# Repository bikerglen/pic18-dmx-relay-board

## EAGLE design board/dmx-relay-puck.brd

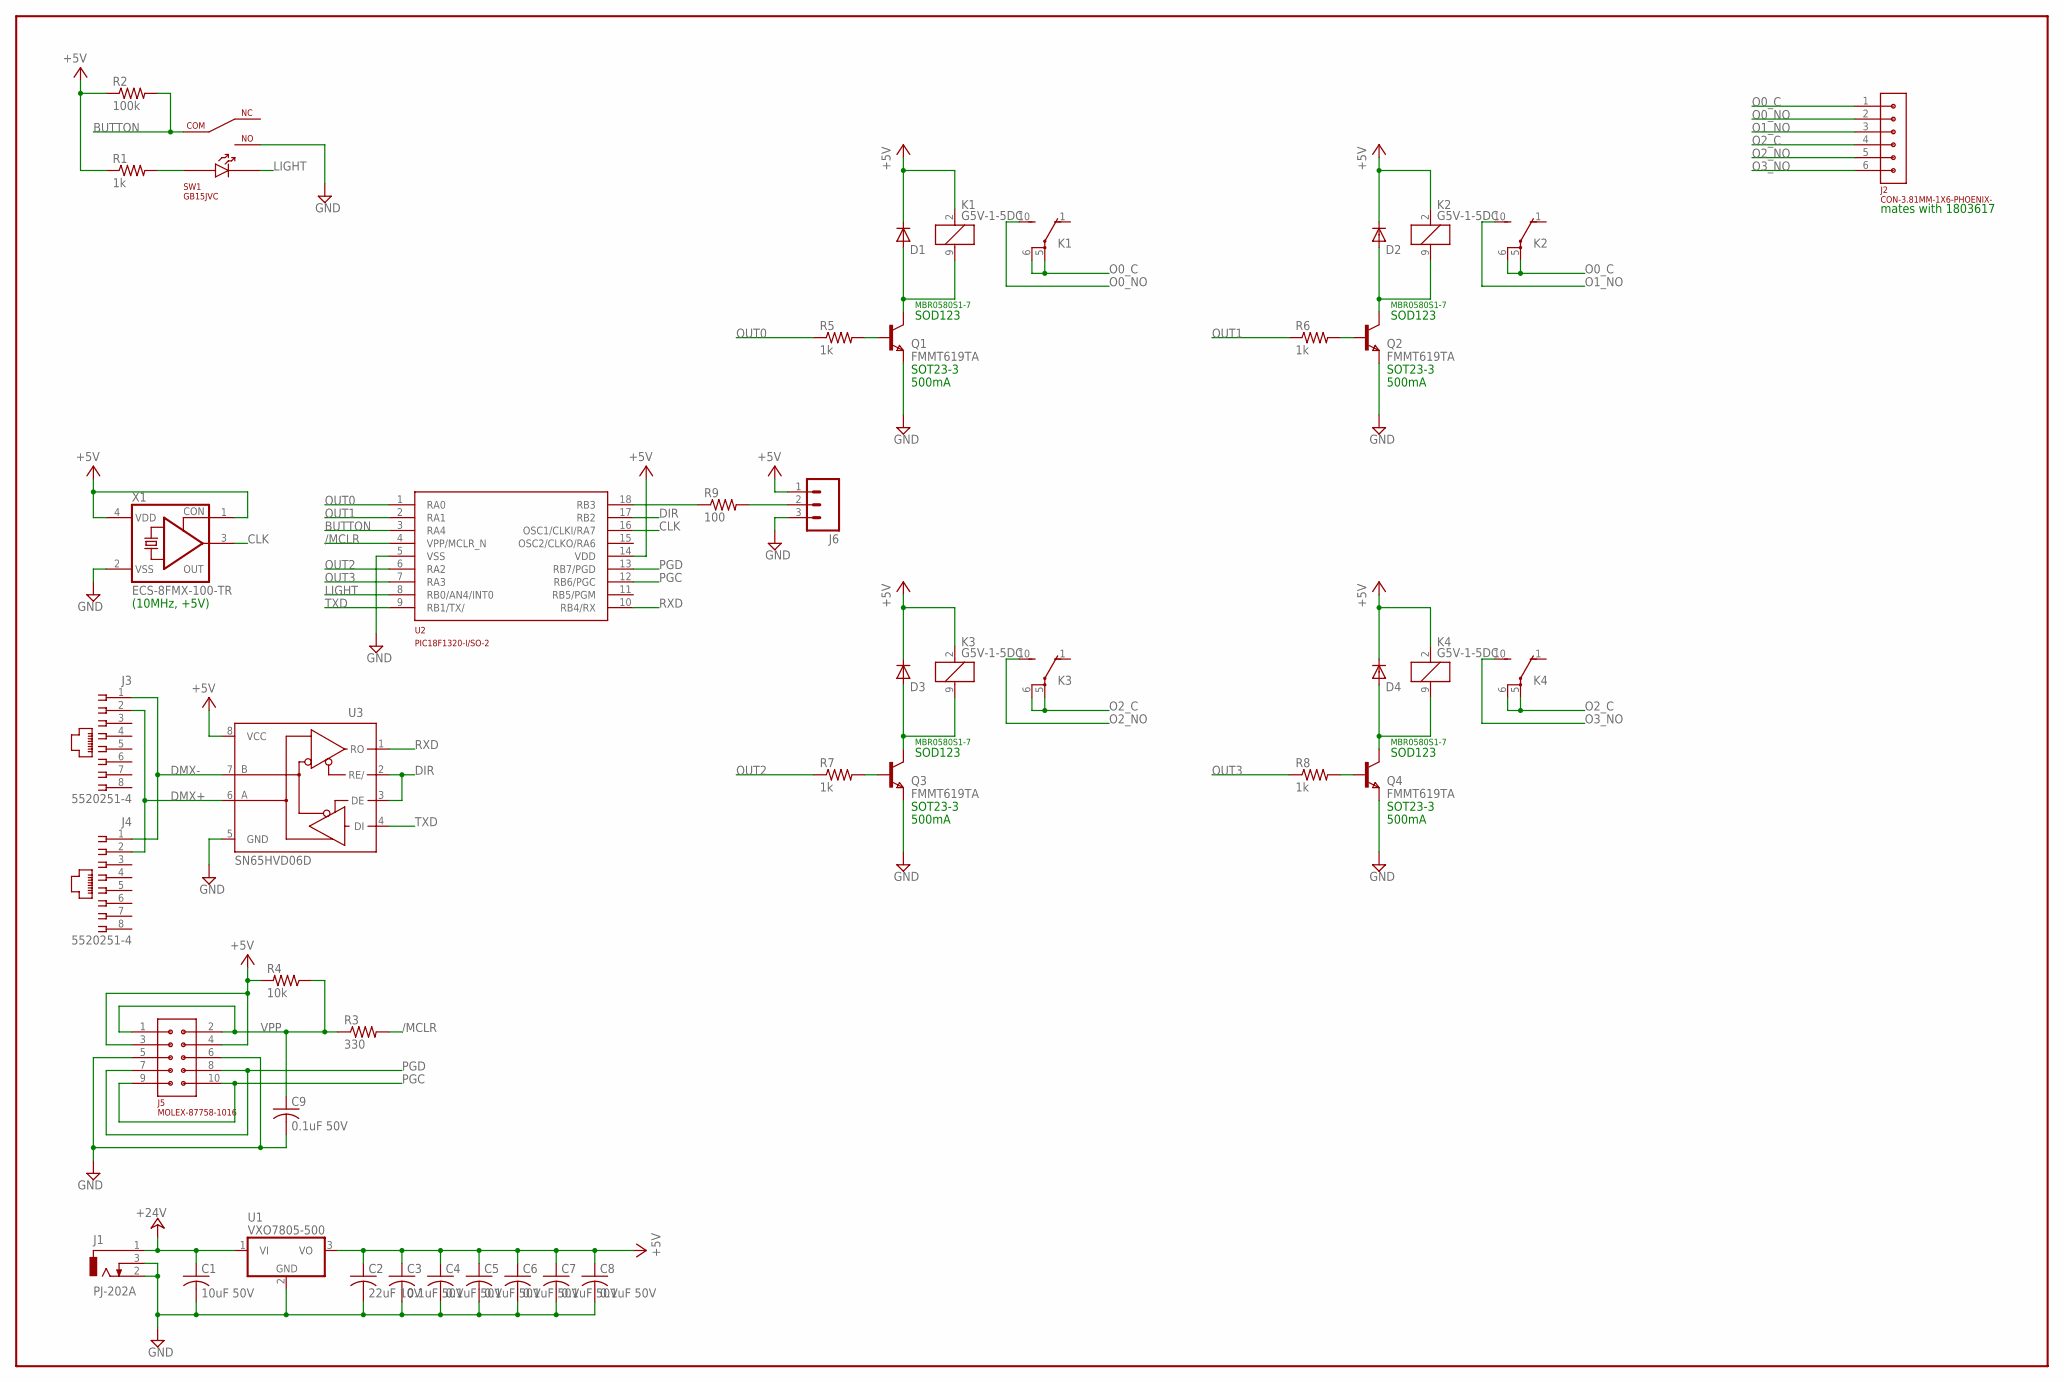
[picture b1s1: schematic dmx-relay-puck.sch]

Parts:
C1: 10uF 50V; C1210K; MFR_PART_NO C1210C106K5RACTU
C2: 22uF 10V; C1206K; MFR_PART_NO C1206C226K8RAC7800
C3, C4, C5, C6, C7, C8, C9: 0.1uF 50V; C1206K; MFR_PART_NO C1206S104M5RACTU
D1, D2, D3, D4: 1N4148W-TP; SOD123; MFR_PART_NO MBR0580S1-7
J1: PJ-202A; DCJ0202; MFR_PART_NO PJ-202A
J2: CON-3.81MM-1X6-PHOENIX-; CON-PHOENIX-3.81-1X6; MFR_PART_NO 1803316
J3, J4: 5520251-4; 520251-4; MFR_PART_NO 5520251-4
J5: MOLEX-87758-1016; CON-2MM-2X5; MFR_PART_NO 87758-1016
J6: M03PTH; 1X03; MFR_PART_NO 61300311121
K1, K2, K3, K4: G5V-1-5DC; G5V1; MFR_PART_NO G5V-1-DC5
Q1, Q2, Q3, Q4: FMMT619TA; SOT-23; MFR_PART_NO FMMT619TA
R1: 1k; R1206; MFR_PART_NO CR1206-JW-102GLF
R2: 100k; R1206; MFR_PART_NO CR1206-JW-104GLF
R3: 330; R1206; MFR_PART_NO CR1206-JW-331ELF
R4: 10k; R1206; MFR_PART_NO CR1206-JW-103GLF
R5, R6, R7, R8: 1k; R1206; MFR_PART_NO CR1206-JW-102ELF
R9: 100; R1206; MFR_PART_NO CR1206-JW-101ELF
SW1: GB15JVC; GB15JHC; MFR_PART_NO GB15JVC
U1: VXO7805-500; CUI-78XX-500; MFR_PART_NO VXO7805-500
U2: PIC18F1320-I/SO-2; SO18W; MFR_PART_NO PIC18F1320-I/SO
U3: SN65HVD06D; SO08; MFR_PART_NO SN65HVD06D
X1: ECS-8FMX-100-TR; 1100S; MFR_PART_NO ECS-8FMX-100-TR

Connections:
+5V: C2.1, C3.1, C4.1, C5.1, C6.1, C7.1, C8.1, D1.C, D2.C, D3.C, D4.C, J5.3, J5.4, J6.1, K1.2 (1), K2.2 (1), K3.2 (1), K4.2 (1), R1.1, R2.1, R4.2, U1.3 (VO), U2.14 (VDD), U3.8 (VCC), X1.1 (CON), X1.4 (VDD)
+24V: C1.1, J1.1, U1.1 (VI)
/MCLR: R3.2, U2.4 (VPP/MCLR_N)
BUTTON: R2.2, SW1.5, U2.3 (RA4)
CLK: U2.16 (OSC1/CLKI/RA7), X1.3 (OUT)
DIR: U2.17 (RB2), U3.2 (RE/), U3.3 (DE)
DMX+: J3.2, J4.2, U3.6 (A)
DMX-: J3.1, J4.1, U3.7 (B)
GND: C1.2, C2.2, C3.2, C4.2, C5.2, C6.2, C7.2, C8.2, C9.2, J1.2, J1.3, J5.5, J5.6, J6.3, Q1.2 (E), Q2.2 (E), Q3.2 (E), Q4.2 (E), SW1.4, U1.2 (GND), U2.5 (VSS), U3.5 (GND), X1.2 (VSS)
LIGHT: SW1.3, U2.8 (RB0/AN4/INT0)
unnamed: Q2.3 (B), R6.2
unnamed: D2.A, K2.9 (2), Q2.1 (C)
unnamed: Q3.3 (B), R7.2
unnamed: D3.A, K3.9 (2), Q3.1 (C)
unnamed: Q4.3 (B), R8.2
unnamed: D4.A, K4.9 (2), Q4.1 (C)
unnamed: R9.1, U2.18 (RB3)
unnamed: J6.2, R9.2
unnamed: R1.2, SW1.1
unnamed: Q1.3 (B), R5.2
unnamed: D1.A, K1.9 (2), Q1.1 (C)
O0_C: J2.1, K1.5, K1.6, K2.5, K2.6
O0_NO: J2.2, K1.10 (S)
O1_NO: J2.3, K2.10 (S)
O2_C: J2.4, K3.5, K3.6, K4.5, K4.6
O2_NO: J2.5, K3.10 (S)
O3_NO: J2.6, K4.10 (S)
OUT0: R5.1, U2.1 (RA0)
OUT1: R6.1, U2.2 (RA1)
OUT2: R7.1, U2.6 (RA2)
OUT3: R8.1, U2.7 (RA3)
PGC: J5.9, J5.10, U2.12 (RB6/PGC)
PGD: J5.7, J5.8, U2.13 (RB7/PGD)
RXD: U2.10 (RB4/RX), U3.1 (RO)
TXD: U2.9 (RB1/TX/), U3.4 (DI)
VPP: C9.1, J5.1, J5.2, R3.1, R4.1

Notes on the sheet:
(10MHz, +5V)
SOD123
SOT23-3
500mA
MBR0580S1-7
mates with 1803617

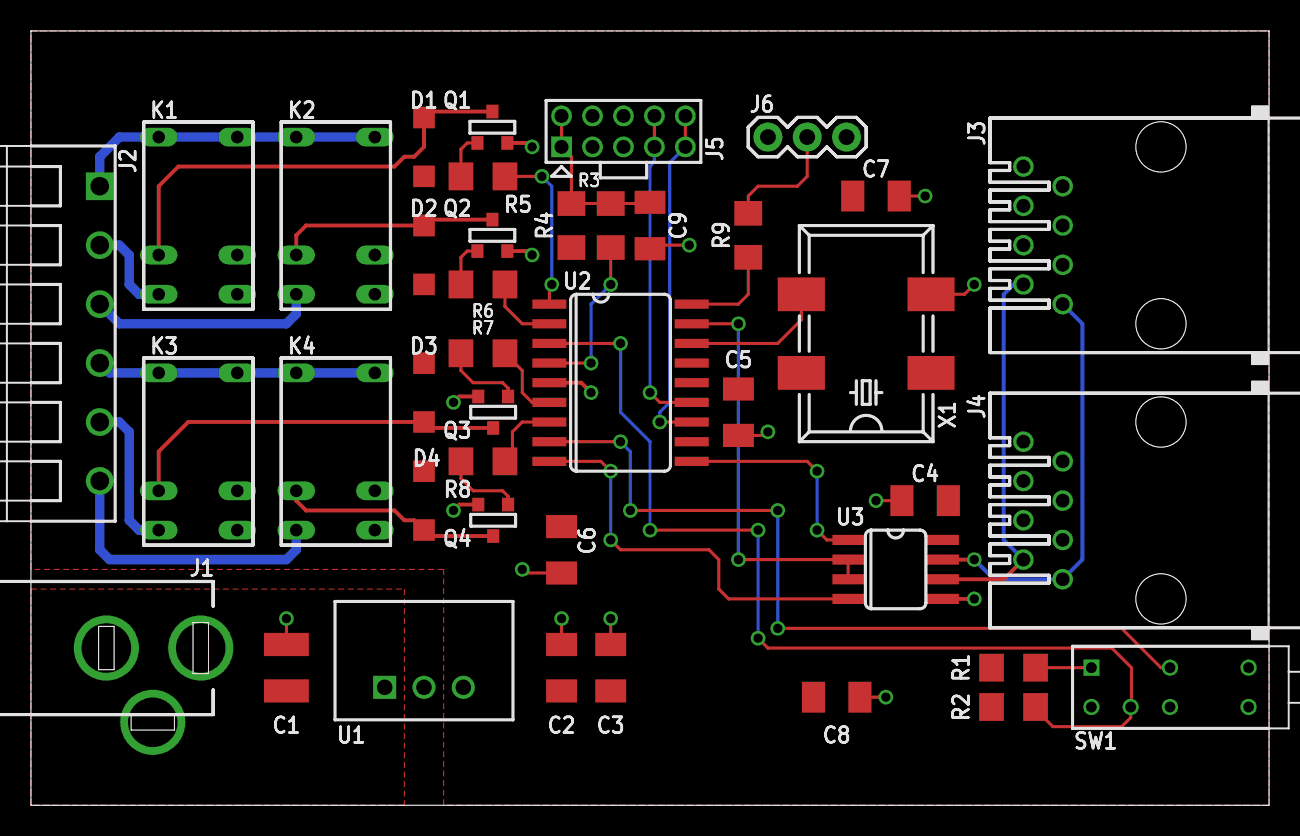
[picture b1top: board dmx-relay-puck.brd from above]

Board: 2 copper layers, 80.0 x 50.0 mm, 41 parts (0 on the bottom side), 36 nets.

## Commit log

2017-09-29 initial checkin
2017-10-01 updated with notes on part substitutions and part stuffing
2017-10-01 initial checkin of front and rear panels
